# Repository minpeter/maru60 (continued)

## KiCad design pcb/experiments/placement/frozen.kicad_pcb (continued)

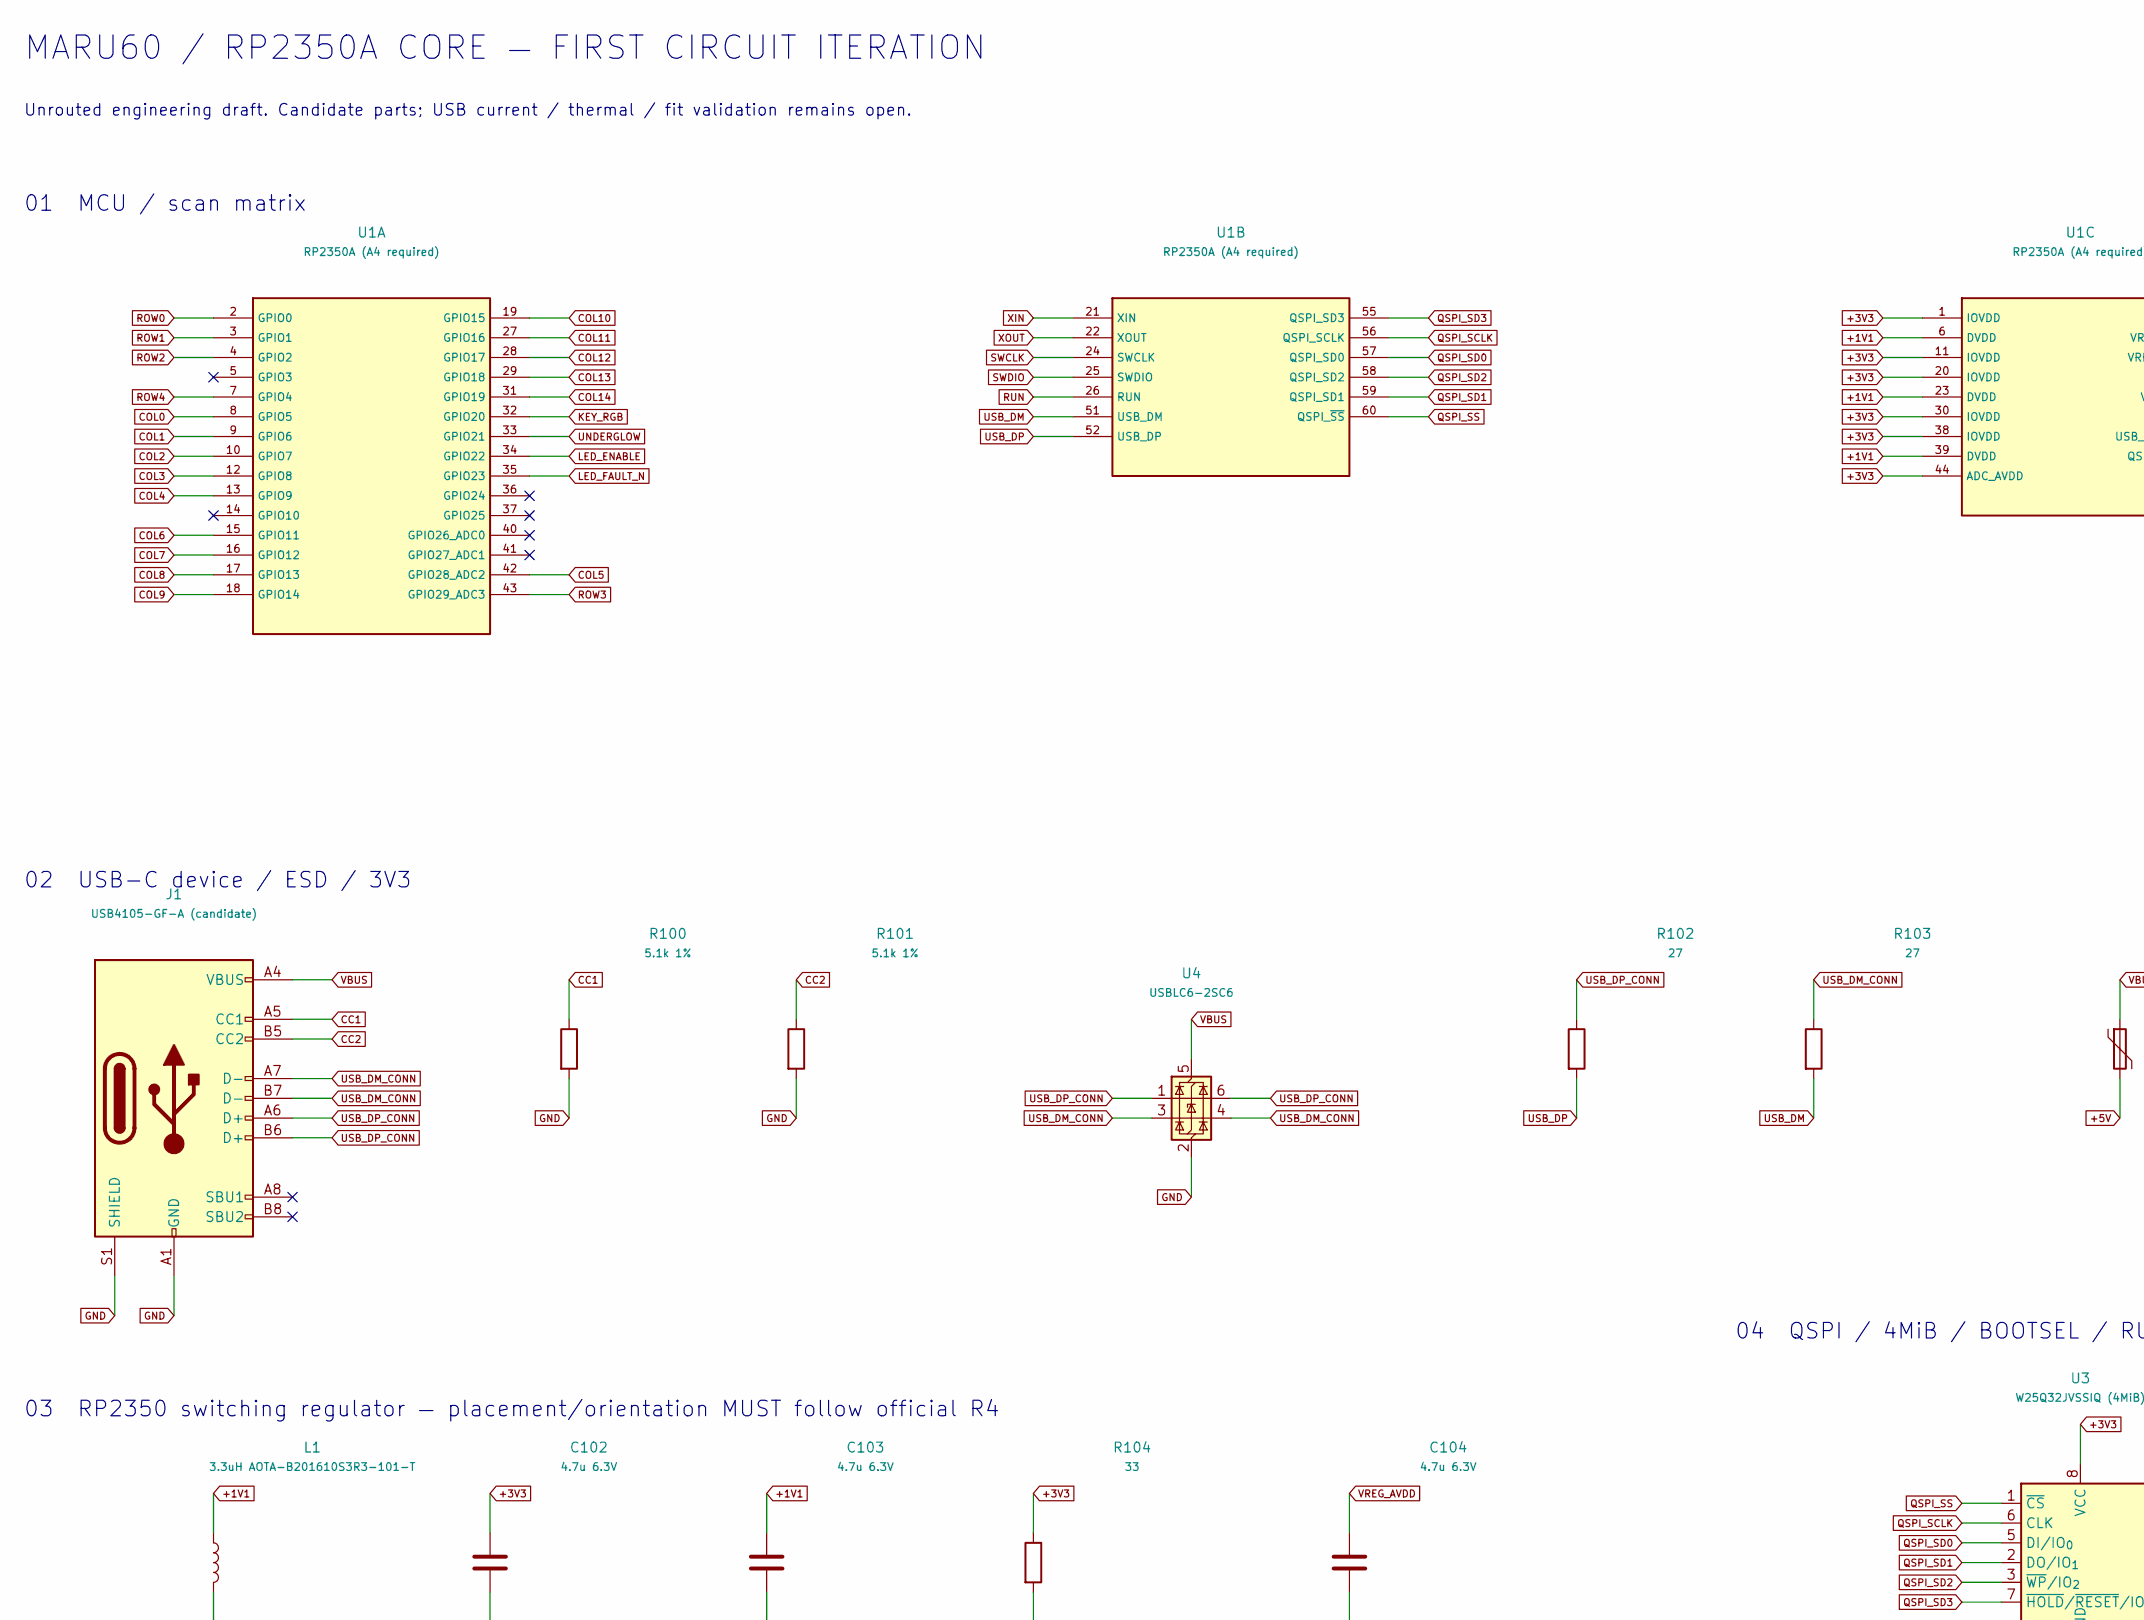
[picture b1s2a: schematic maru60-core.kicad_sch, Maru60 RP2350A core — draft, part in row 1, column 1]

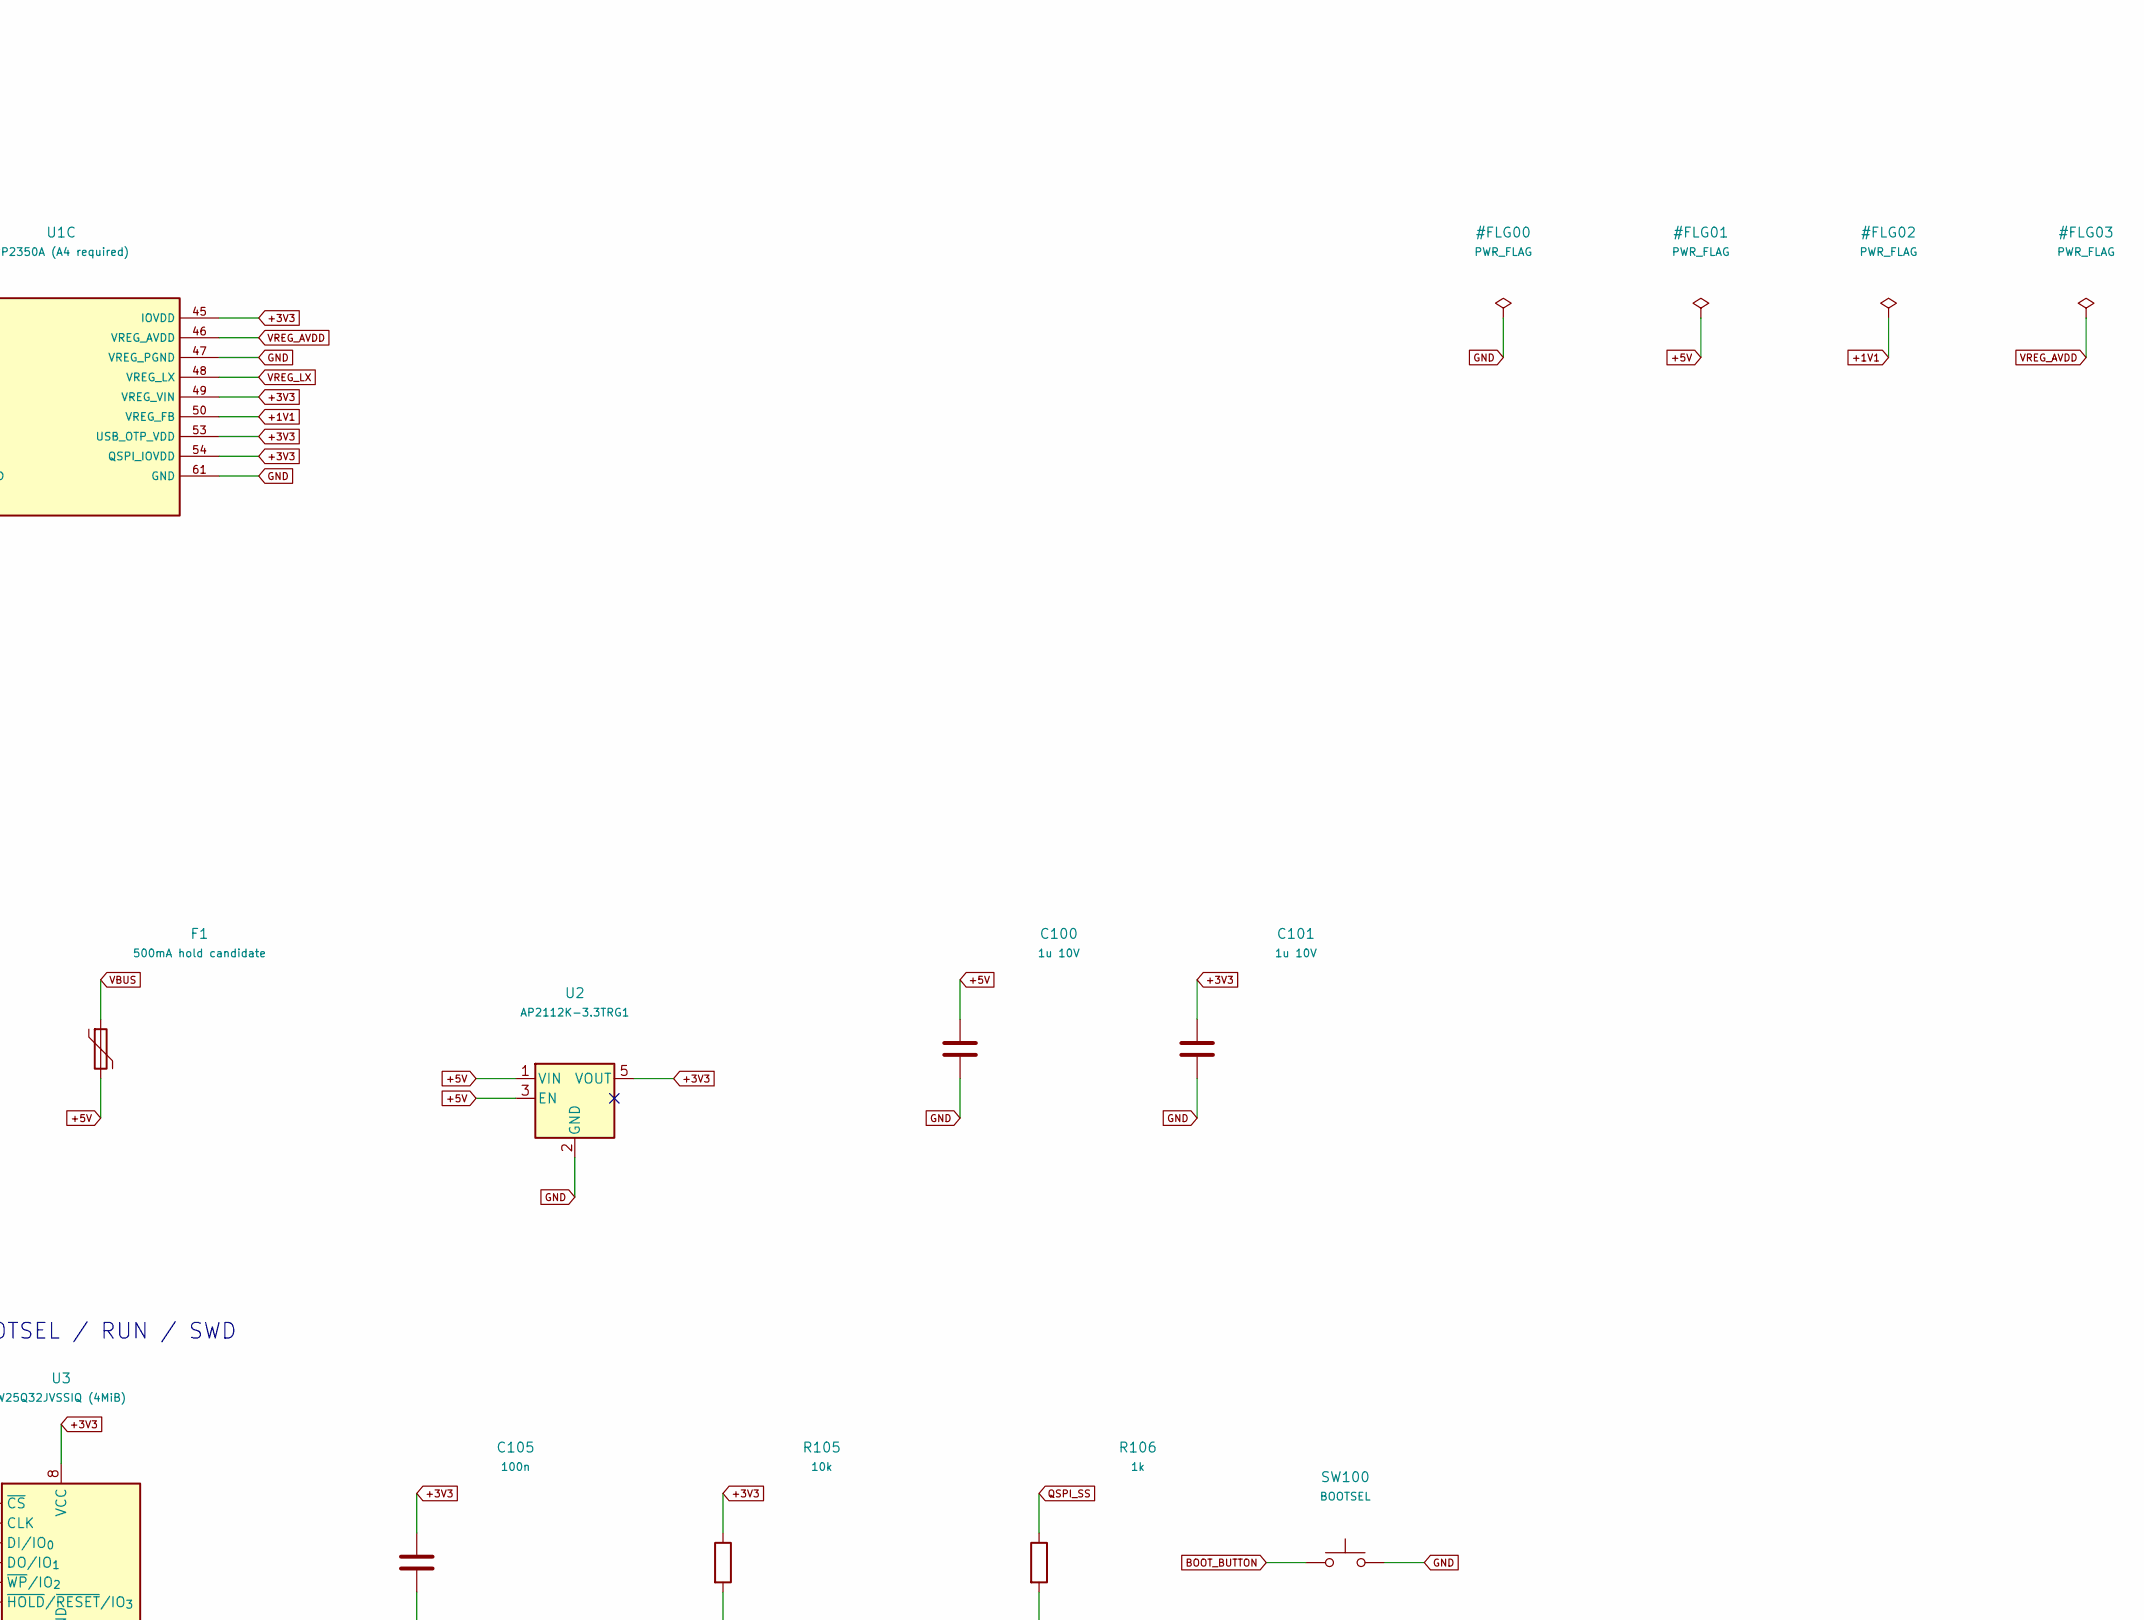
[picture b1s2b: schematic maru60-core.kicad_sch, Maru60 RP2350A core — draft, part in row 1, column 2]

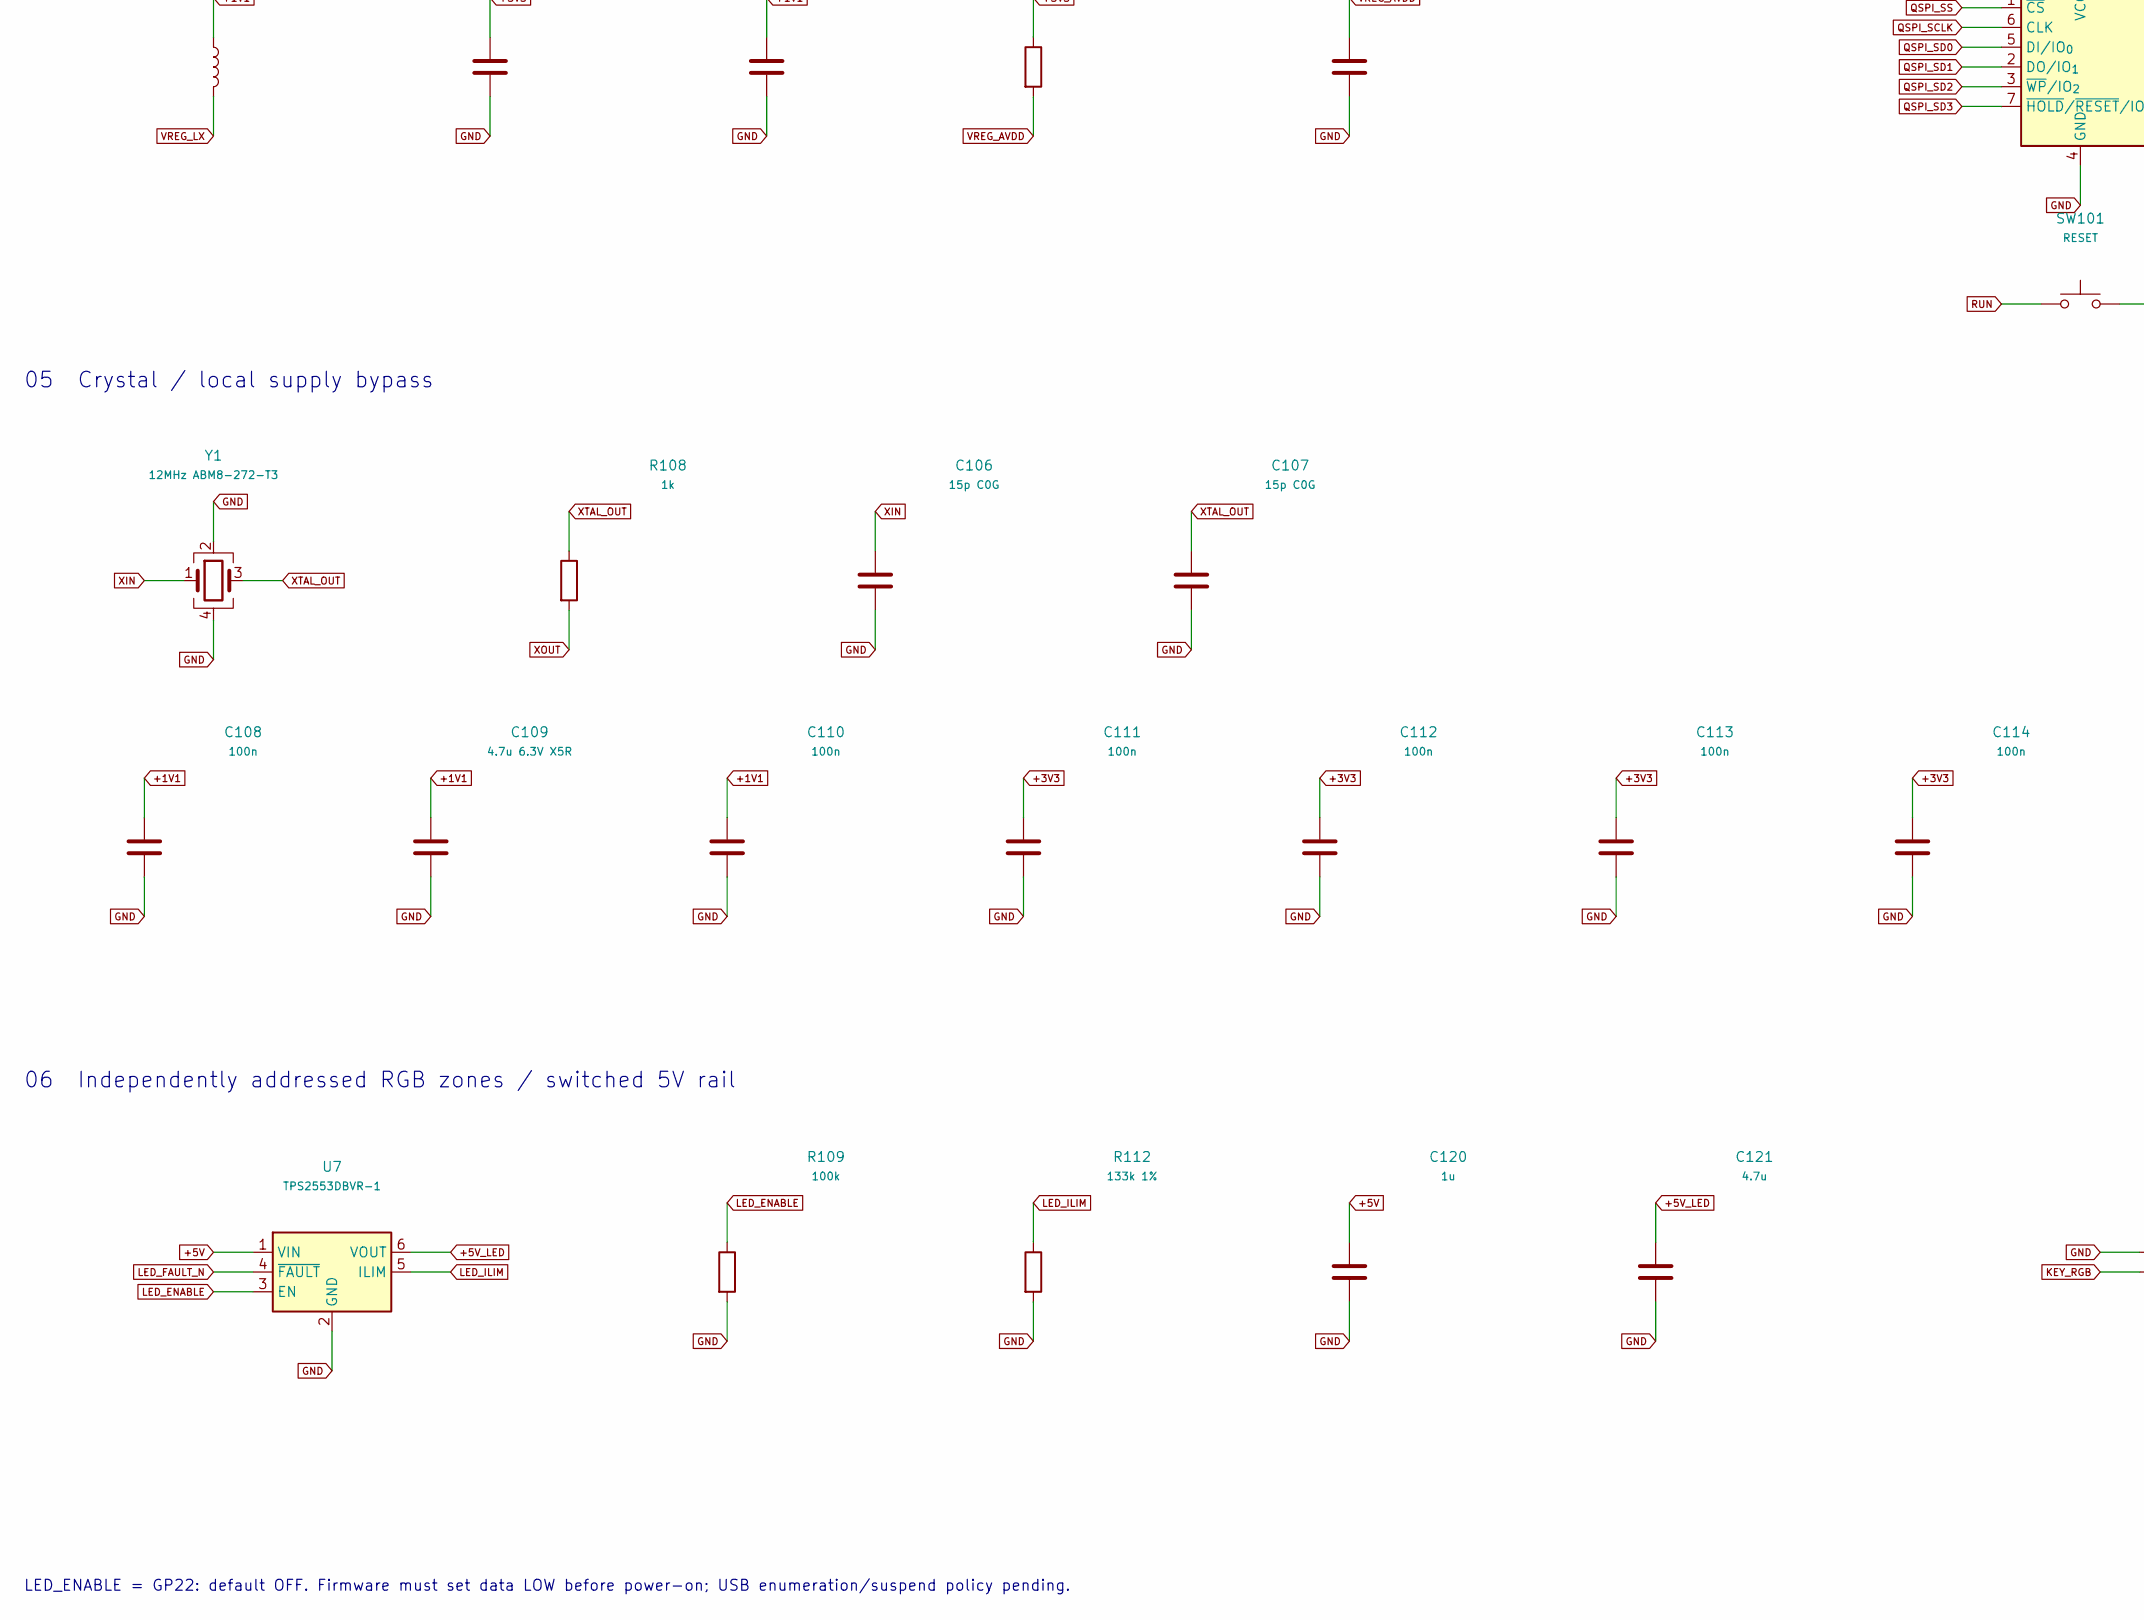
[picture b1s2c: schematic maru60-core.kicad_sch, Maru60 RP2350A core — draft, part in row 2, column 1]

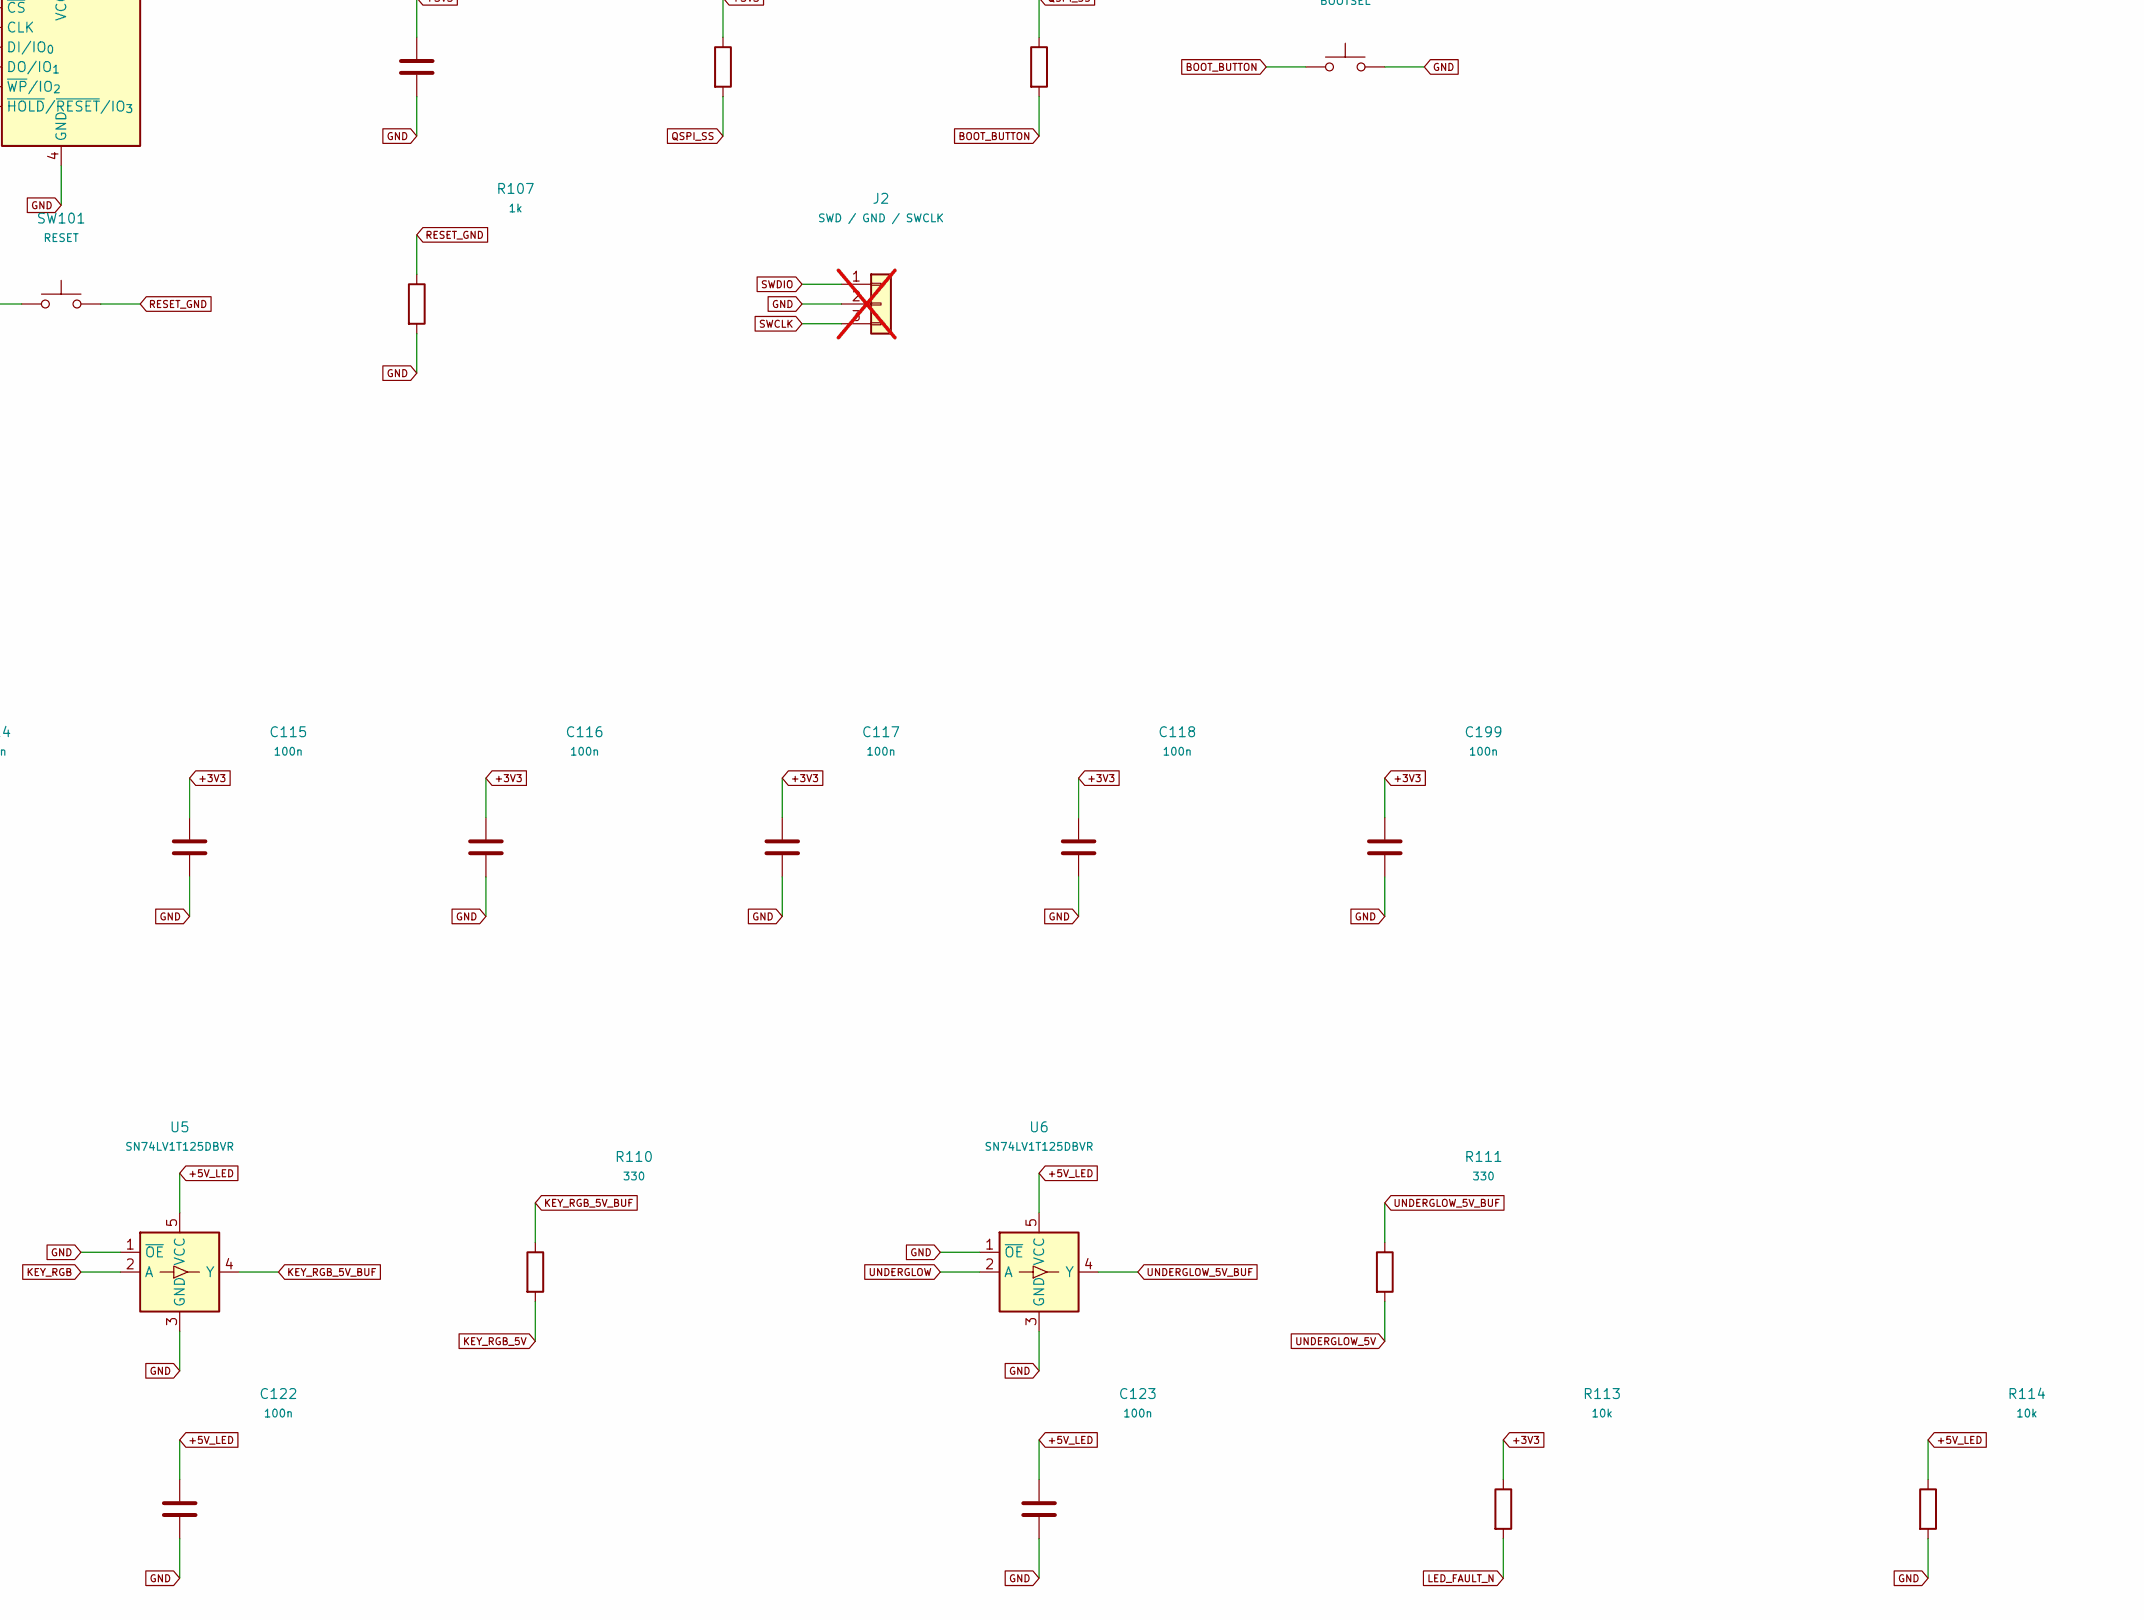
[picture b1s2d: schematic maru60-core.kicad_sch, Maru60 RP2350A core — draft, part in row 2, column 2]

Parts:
C100, C101: 1u 10V; C_0402_1005Metric
C102, C103: 4.7u 6.3V; C_0402_Official_R4_Wide; Part_Selection_Status Inherited reference MPN only; Maru60 pa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
C104: 4.7u 6.3V; C_0402_1005Metric
C105, C108, C110, C111, C112, C113, C114, C115, C116, C117, C118, C122, C123: 100n; C_0402_1005Metric
C106, C107: 15p C0G; C_0402_1005Metric
C109: 4.7u 6.3V X5R; C_0402_1005Metric
C120: 1u; C_0402_1005Metric
C121: 4.7u; C_0402_1005Metric
C199: 100n; C_0402_1005Metric; manufacturer_pn GRM155R71E104KE14D
F1: 500mA hold candidate; Fuse_1206_3216Metric
J1: USB4105-GF-A (candidate); USB_C_Receptacle_GCT_USB4105-xx-A_16P_TopMnt_Horizontal
J2: SWD / GND / SWCLK; PinHeader_1x03_P2.54mm_Vertical; not fitted
L1: 3.3uH AOTA-B201610S3R3-101-T; Abracon_AOTA_B201610S3R3_Official_R4; Part_Selection_Status Inherited reference MPN only; Maru60 pa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
R100, R101: 5.1k 1%; R_0402_1005Metric
R102, R103: 27; R_0402_1005Metric
R104: 33; R_0402_1005Metric
R105, R113, R114: 10k; R_0402_1005Metric
R106, R107, R108: 1k; R_0402_1005Metric
R109: 100k; R_0402_1005Metric
R110, R111: 330; R_0402_1005Metric
R112: 133k 1%; R_0402_1005Metric
SW100: BOOTSEL; SW_SPST_TL3342
SW101: RESET; SW_SPST_TL3342
U1: RP2350A (A4 required); RP2350A_QFN60_Official_R4; manufacturer_pn RP2350A
U2: AP2112K-3.3TRG1; SOT-23-5
U3: W25Q32JVSSIQ (4MiB); SOIC-8_5.3x5.3mm_P1.27mm
U4: USBLC6-2SC6; SOT-23-6
U5, U6: SN74LV1T125DBVR; SOT-23-5
U7: TPS2553DBVR-1; SOT-23-6
Y1: 12MHz ABM8-272-T3; Crystal_SMD_3225-4Pin_3.2x2.5mm

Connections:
+1V1: C103.1, C108.1, C109.1, C110.1, L1.1, U1.6 (DVDD), U1.23 (DVDD), U1.39 (DVDD), U1.50 (VREG_FB)
+3V3: C101.1, C102.1, C105.1, C111.1, C112.1, C113.1, C114.1, C115.1, C116.1, C117.1, C118.1, C199.1, R104.1, R105.1, R113.1, U1.1 (IOVDD), U1.11 (IOVDD), U1.20 (IOVDD), U1.30 (IOVDD), U1.38 (IOVDD), U1.44 (ADC_AVDD), U1.45 (IOVDD), U1.49 (VREG_VIN), U1.53 (USB_OTP_VDD), U1.54 (QSPI_IOVDD), U2.5 (VOUT), U3.8 (VCC)
+5V: C100.1, C120.1, F1.2, U2.1 (VIN), U2.3 (EN), U7.1 (VIN)
+5V_LED: C121.1, C122.1, C123.1, R114.1, U5.5 (VCC), U6.5 (VCC), U7.6 (VOUT); also elsewhere on the board
BOOT_BUTTON: R106.2, SW100.1
CC1: J1.A5 (CC1), R100.1
CC2: J1.B5 (CC2), R101.1
COL0: U1.8 (GPIO5); also elsewhere on the board
COL1: U1.9 (GPIO6); also elsewhere on the board
COL2: U1.10 (GPIO7); also elsewhere on the board
COL7: U1.16 (GPIO12); also elsewhere on the board
COL8: U1.17 (GPIO13); also elsewhere on the board
COL9: U1.18 (GPIO14); also elsewhere on the board
COL13: U1.29 (GPIO18); also elsewhere on the board
COL14: U1.31 (GPIO19); also elsewhere on the board
GND: C100.2, C101.2, C102.2, C103.2, C104.2, C105.2, C106.2, C107.2, C108.2, C109.2, C110.2, C111.2, C112.2, C113.2, C114.2, C115.2, C116.2, C117.2, C118.2, C120.2, C121.2, C122.2, C123.2, C199.2, J1.A1 (GND), J1.A12 (GND), J1.B1 (GND), J1.B12 (GND), J1.S1 (SHIELD), J2.2, R100.2, R101.2, R107.2, R109.2, R112.2, R114.2, SW100.2, U1.47 (VREG_PGND), U1.61 (GND), U2.2 (GND), U3.4 (GND), U4.2 (GND), U5.1 (~OE), U5.3 (GND), U6.1 (~OE), U6.3 (GND), U7.2 (GND), Y1.2, Y1.4; also elsewhere on the board
KEY_RGB: U1.32 (GPIO20), U5.2 (A)
KEY_RGB_5V: R110.2; also elsewhere on the board
KEY_RGB_5V_BUF: R110.1, U5.4 (Y)
LED_ENABLE: R109.1, U1.34 (GPIO22), U7.3 (EN)
LED_FAULT_N: R113.2, U1.35 (GPIO23), U7.4 (~FAULT)
LED_ILIM: R112.1, U7.5 (ILIM)
QSPI_SCLK: U1.56 (QSPI_SCLK), U3.6 (CLK)
QSPI_SD0: U1.57 (QSPI_SD0), U3.5 (DI/IO_{0})
QSPI_SD1: U1.59 (QSPI_SD1), U3.2 (DO/IO_{1})
QSPI_SD2: U1.58 (QSPI_SD2), U3.3 (~WP/IO_{2})
QSPI_SD3: U1.55 (QSPI_SD3), U3.7 (~HOLD/~RESET/IO_{3})
QSPI_SS: R105.2, R106.1, U1.60 (QSPI_~SS), U3.1 (~CS)
RESET_GND: R107.1, SW101.2
ROW0: U1.2 (GPIO0); also elsewhere on the board
ROW1: U1.3 (GPIO1); also elsewhere on the board
ROW2: U1.4 (GPIO2); also elsewhere on the board
ROW3: U1.5 (GPIO3); also elsewhere on the board
ROW4: U1.7 (GPIO4); also elsewhere on the board
RUN: SW101.1, U1.26 (RUN)
SWCLK: J2.3, U1.24 (SWCLK)
SWDIO: J2.1, U1.25 (SWDIO)
UNDERGLOW: U1.33 (GPIO21), U6.2 (A)
UNDERGLOW_5V: R111.2; also elsewhere on the board
UNDERGLOW_5V_BUF: R111.1, U6.4 (Y)
USB_DM: R103.2, U1.51 (USB_DM)
USB_DM_CONN: J1.A7 (D-), J1.B7 (D-), R103.1, U4.3 (I/O2), U4.4 (I/O2)
USB_DP: R102.2, U1.52 (USB_DP)
USB_DP_CONN: J1.A6 (D+), J1.B6 (D+), R102.1, U4.1 (I/O1), U4.6 (I/O1)
VBUS: F1.1, J1.A4 (VBUS), J1.A9 (VBUS), J1.B4 (VBUS), J1.B9 (VBUS), U4.5 (VBUS)
VREG_AVDD: C104.1, R104.2, U1.46 (VREG_AVDD)
VREG_LX: L1.2, U1.48 (VREG_LX)
XIN: C106.1, U1.21 (XIN), Y1.1
XOUT: R108.2, U1.22 (XOUT)
XTAL_OUT: C107.1, R108.1, Y1.3

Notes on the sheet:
MARU60 / RP2350A CORE — FIRST CIRCUIT ITERATION
Unrouted engineering draft. Candidate parts; USB current / thermal / fit validation remains open.
01 MCU / scan matrix
02 USB-C device / ESD / 3V3
03 RP2350 switching regulator — placement/orientation MUST follow official R4
04 QSPI / 4MiB / BOOTSEL / RUN / SWD
05 Crystal / local supply bypass
06 Independently addressed RGB zones / switched 5V rail
LED_ENABLE = GP22: default OFF. Firmware must set data LOW before power-on; USB enumeration/suspend policy pending.
